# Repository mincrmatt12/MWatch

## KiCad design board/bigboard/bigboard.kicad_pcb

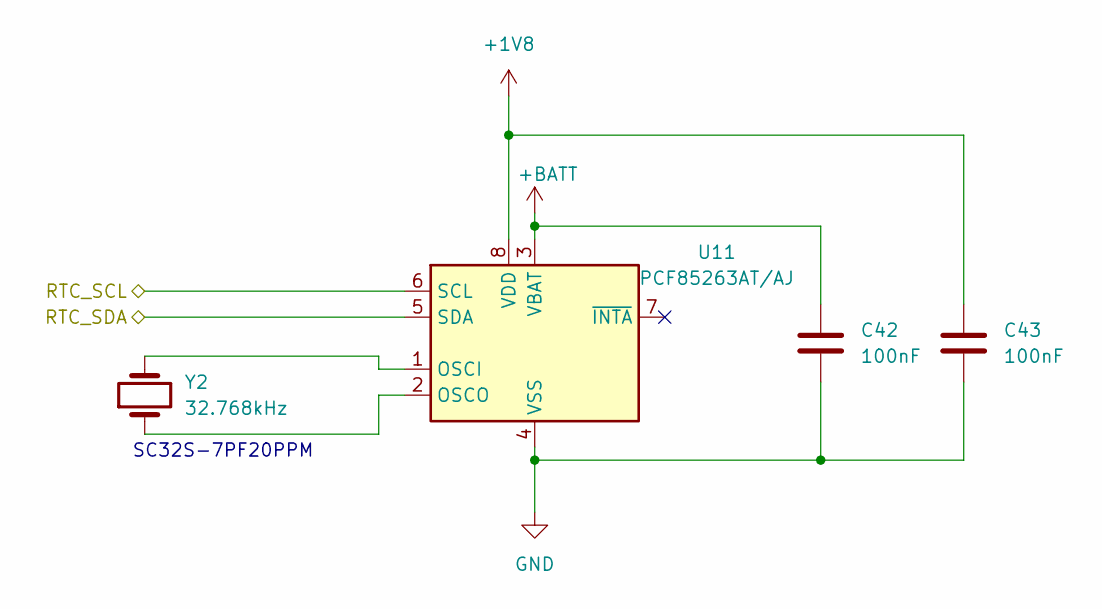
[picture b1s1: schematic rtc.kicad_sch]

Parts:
C42, C43: 100nF; C_0201_0603Metric; MPN CC0201KRX5R8BB104
U11: PCF85263AT/AJ; SOIC-8_3.9x4.9mm_P1.27mm; MPN PCF85263AT/AJ
Y2: 32.768kHz; Crystal_SMD_3215-2Pin_3.2x1.5mm; MPN SC32S-7PF20PPM

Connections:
+1V8: C43.1, U11.8 (VDD); also elsewhere on the board
+BATT: C42.1, U11.3 (VBAT); also elsewhere on the board
/BT/SCL_RTC: U11.6 (SCL); also elsewhere on the board
/BT/SDA_RTC: U11.5 (SDA); also elsewhere on the board
GND: C42.2, C43.2, U11.4 (VSS); also elsewhere on the board
unnamed: U11.1 (OSCI), Y2.2
unnamed: U11.2 (OSCO), Y2.1

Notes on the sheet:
SC32S-7PF20PPM

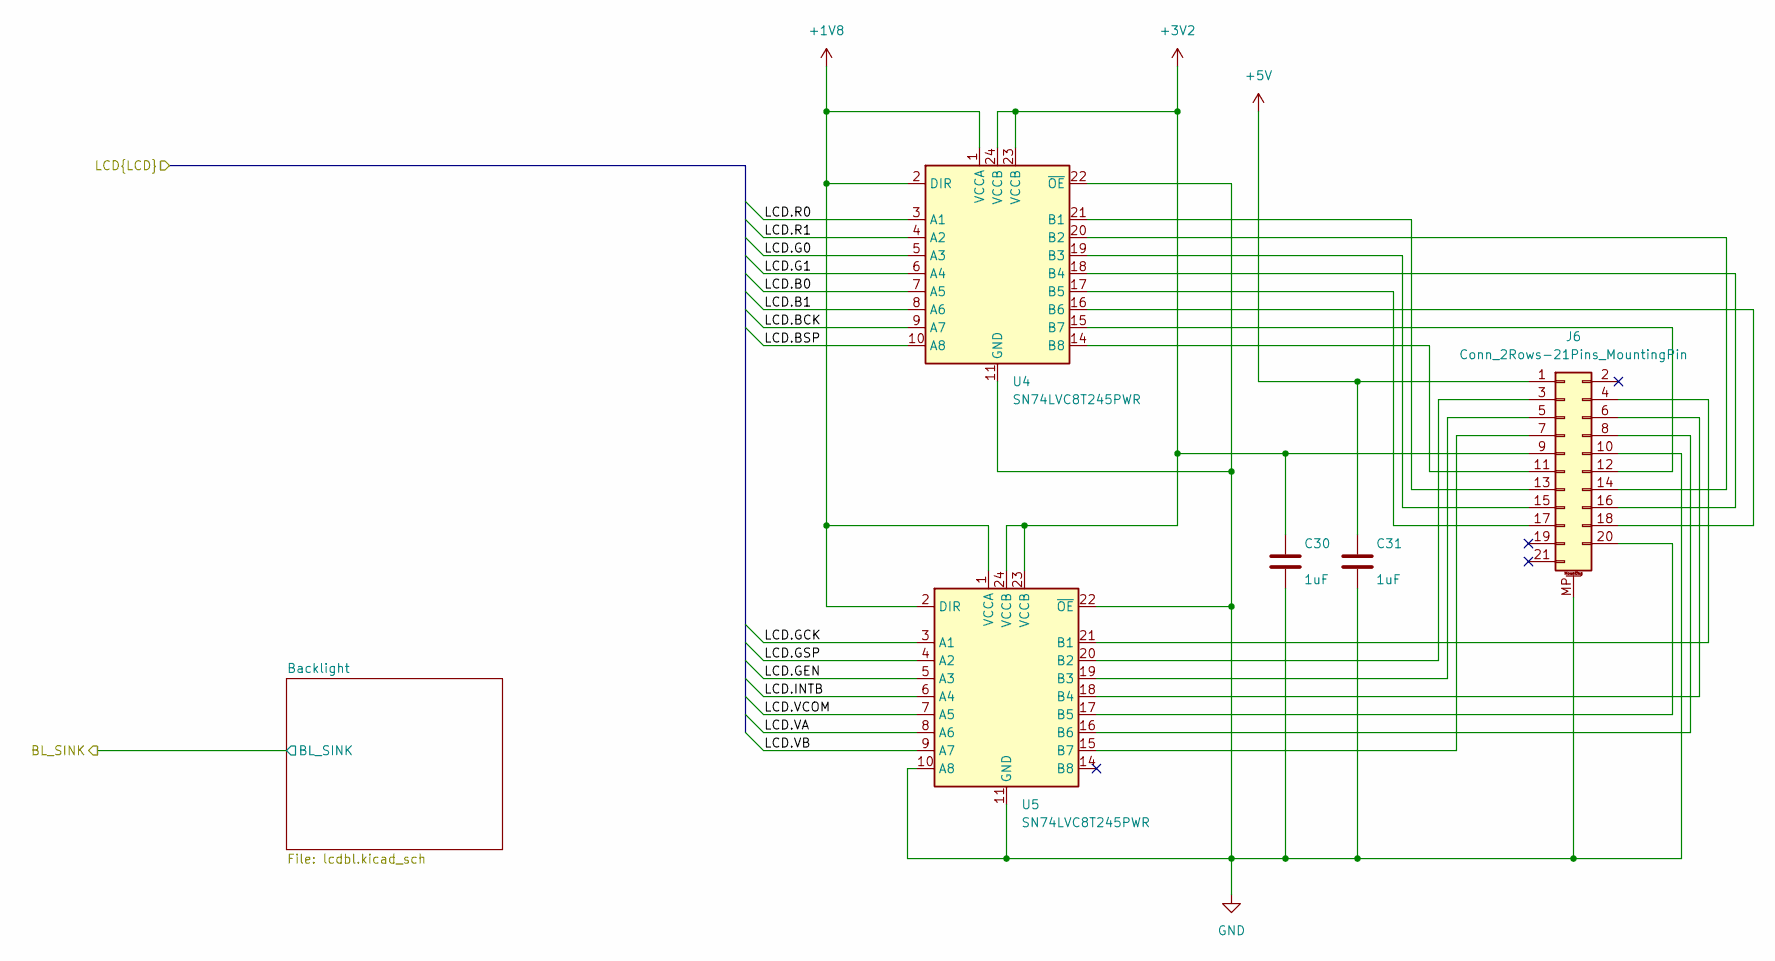
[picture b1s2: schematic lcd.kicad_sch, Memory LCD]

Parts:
C30, C31: 1uF; C_0201_0603Metric; MPN CC0201MRX5R6BB105
J6: Conn_2Rows-21Pins_MountingPin; 5035662102; MPN 503566-2102
U4, U5: SN74LVC8T245PWR; TSSOP-24_4.4x7.8mm_P0.65mm; MPN SN74LVC8T245PWR

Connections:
+1V8: U4.1 (VCCA), U4.2 (DIR), U5.1 (VCCA), U5.2 (DIR); also elsewhere on the board
+3V2: C30.1, J6.9, U4.23 (VCCB), U4.24 (VCCB), U5.23 (VCCB), U5.24 (VCCB); also elsewhere on the board
+5V: C31.1, J6.1; also elsewhere on the board
/LCD/LCD.B0: U4.7 (A5); also elsewhere on the board
/LCD/LCD.B1: U4.8 (A6); also elsewhere on the board
/LCD/LCD.BCK: U4.9 (A7); also elsewhere on the board
/LCD/LCD.BSP: U4.10 (A8); also elsewhere on the board
/LCD/LCD.G0: U4.5 (A3); also elsewhere on the board
/LCD/LCD.G1: U4.6 (A4); also elsewhere on the board
/LCD/LCD.GCK: U5.3 (A1); also elsewhere on the board
/LCD/LCD.GEN: U5.5 (A3); also elsewhere on the board
/LCD/LCD.GSP: U5.4 (A2); also elsewhere on the board
/LCD/LCD.INTB: U5.6 (A4); also elsewhere on the board
/LCD/LCD.R0: U4.3 (A1); also elsewhere on the board
/LCD/LCD.R1: U4.4 (A2); also elsewhere on the board
/LCD/LCD.VA: U5.8 (A6); also elsewhere on the board
/LCD/LCD.VB: U5.7 (A5), U5.9 (A7); also elsewhere on the board
GND: C30.2, C31.2, J6.10, J6.MP (MountPin), U4.11 (GND), U4.12 (GND), U4.13 (GND), U4.22 (~OE), U5.10 (A8), U5.11 (GND), U5.12 (GND), U5.13 (GND), U5.22 (~OE); also elsewhere on the board
unnamed: J6.3, U5.20 (B2)
unnamed: J6.4, U5.21 (B1)
unnamed: J6.5, U5.19 (B3)
unnamed: J6.6, U5.18 (B4)
unnamed: J6.7, U5.15 (B7)
unnamed: J6.8, U5.16 (B6)
unnamed: J6.11, U4.14 (B8)
unnamed: J6.12, U4.15 (B7)
unnamed: J6.13, U4.21 (B1)
unnamed: J6.14, U4.20 (B2)
unnamed: J6.15, U4.19 (B3)
unnamed: J6.16, U4.18 (B4)
unnamed: J6.17, U4.17 (B5)
unnamed: J6.18, U4.16 (B6)
unnamed: J6.20, U5.17 (B5)

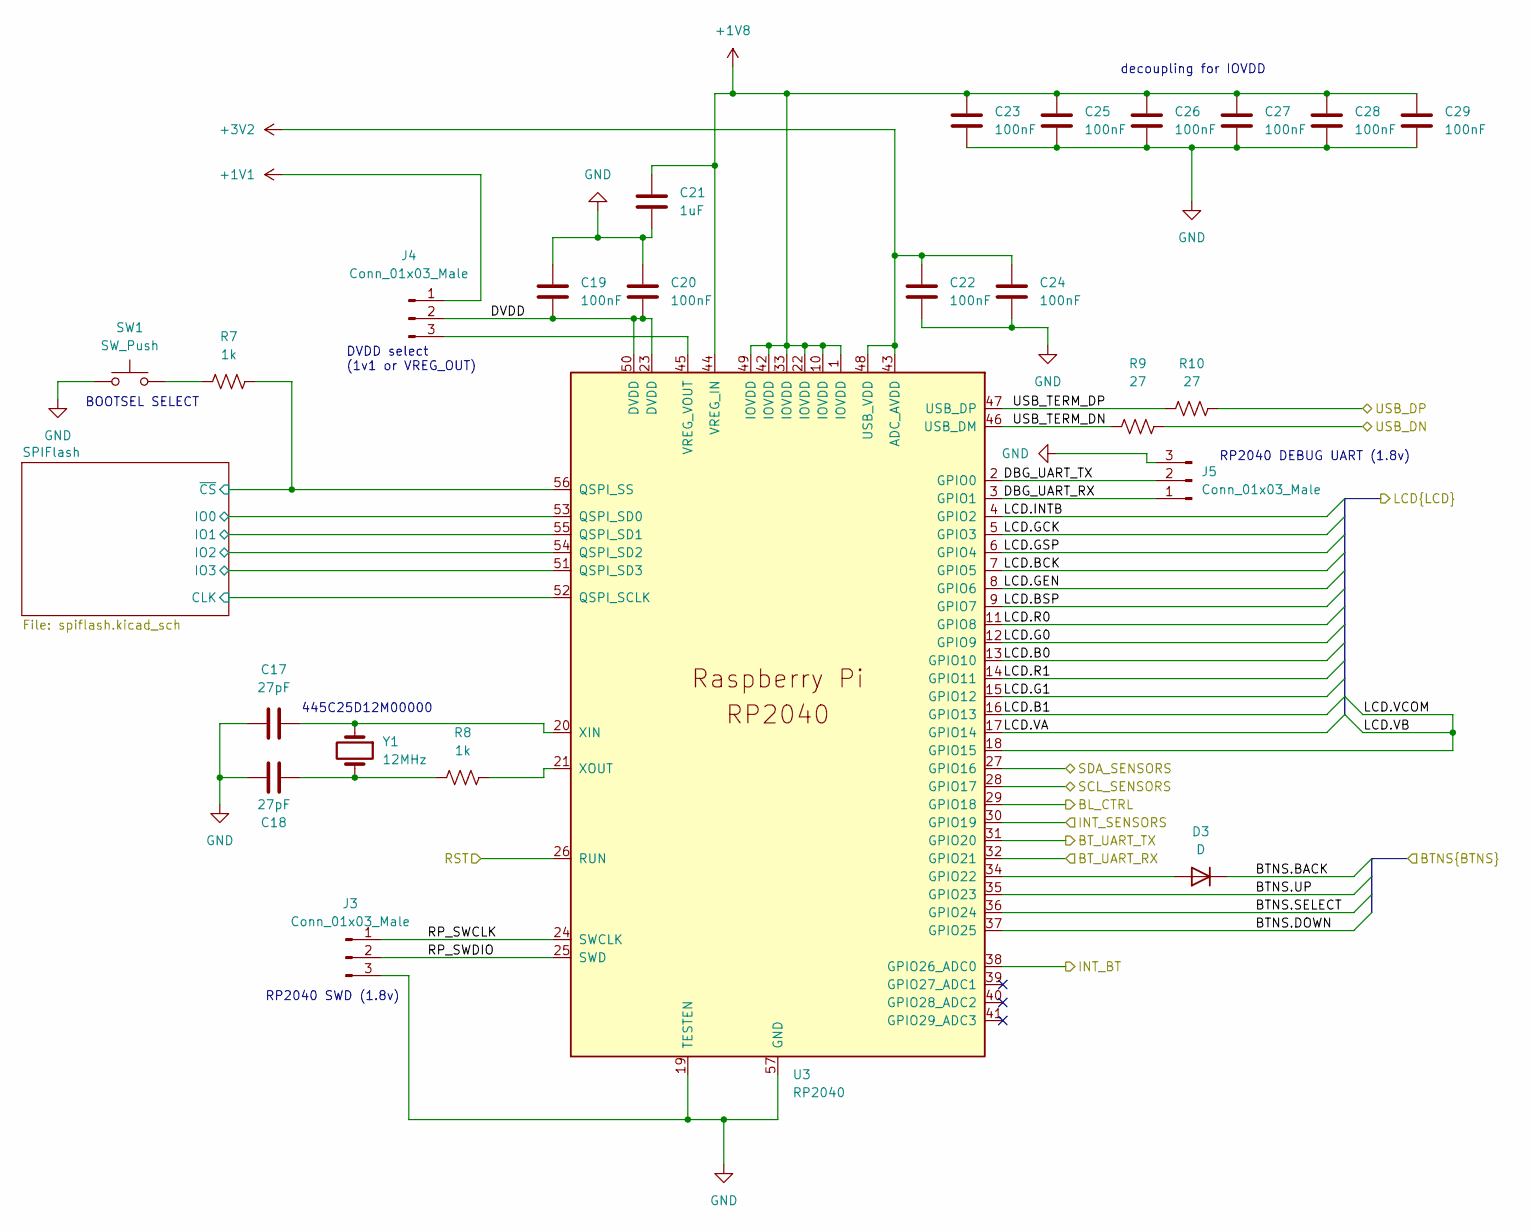
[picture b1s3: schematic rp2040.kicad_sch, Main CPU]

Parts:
C17, C18: 27pF; C_0201_0603Metric; MPN CC0201JRNPO9BN270
C19, C20, C22, C23, C24, C25, C26, C27, C28, C29: 100nF; C_0201_0603Metric; MPN CC0201KRX5R8BB104
C21: 1uF; C_0201_0603Metric; MPN CC0201MRX5R6BB105
D3: D; D_SOD-323; MPN CUS10S30,H3F
J3, J4, J5: Conn_01x03_Male; PinHeader_1x03_P2.54mm_Vertical
R7, R8: 1k; R_0201_0603Metric; MPN RC0201FR-071KL
R9, R10: 27; R_0201_0603Metric; MPN RC0201FR-0727RL
SW1: SW_Push; SW_PUSH_6mm; MPN B3F-1020
U3: RP2040; RP2040-QFN-56; MPN SC0914(7)
Y1: 12MHz; Crystal_SMD_5032-2Pin_5.0x3.2mm; MPN 445C25D12M00000

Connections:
+1V1: J4.1; also elsewhere on the board
+1V8: C21.1, C23.1, C25.1, C26.1, C27.1, C28.1, C29.1, U3.1 (IOVDD), U3.10 (IOVDD), U3.22 (IOVDD), U3.33 (IOVDD), U3.42 (IOVDD), U3.44 (VREG_IN), U3.49 (IOVDD); also elsewhere on the board
+3V2: C22.1, C24.1, U3.43 (ADC_AVDD), U3.48 (USB_VDD); also elsewhere on the board
/BT/BT_INT: U3.38 (GPIO26_ADC0); also elsewhere on the board
/BT/BT_UART_RX: U3.31 (GPIO20); also elsewhere on the board
/BT/BT_UART_TX: U3.32 (GPIO21); also elsewhere on the board
/ButtonsHaptics/BTNS.BACK: D3.1 (K); also elsewhere on the board
/ButtonsHaptics/BTNS.DOWN: U3.37 (GPIO25); also elsewhere on the board
/ButtonsHaptics/BTNS.SELECT: U3.36 (GPIO24); also elsewhere on the board
/ButtonsHaptics/BTNS.UP: U3.35 (GPIO23); also elsewhere on the board
/DbgResets/RP2040_RST: U3.26 (RUN); also elsewhere on the board
/LCD/LCD.B0: U3.13 (GPIO10); also elsewhere on the board
/LCD/LCD.B1: U3.16 (GPIO13); also elsewhere on the board
/LCD/LCD.BCK: U3.7 (GPIO5); also elsewhere on the board
/LCD/LCD.BSP: U3.9 (GPIO7); also elsewhere on the board
/LCD/LCD.G0: U3.12 (GPIO9); also elsewhere on the board
/LCD/LCD.G1: U3.15 (GPIO12); also elsewhere on the board
/LCD/LCD.GCK: U3.5 (GPIO3); also elsewhere on the board
/LCD/LCD.GEN: U3.8 (GPIO6); also elsewhere on the board
/LCD/LCD.GSP: U3.6 (GPIO4); also elsewhere on the board
/LCD/LCD.INTB: U3.4 (GPIO2); also elsewhere on the board
/LCD/LCD.R0: U3.11 (GPIO8); also elsewhere on the board
/LCD/LCD.R1: U3.14 (GPIO11); also elsewhere on the board
/LCD/LCD.VA: U3.17 (GPIO14); also elsewhere on the board
/LCD/LCD.VB: U3.18 (GPIO15); also elsewhere on the board
/Power/BL_CTRL/IO1: U3.29 (GPIO18); also elsewhere on the board
/Power/USB_DN: R9.2; also elsewhere on the board
/Power/USB_DP: R10.2; also elsewhere on the board
/RP2040/DBG_UART_RX: J5.1, U3.3 (GPIO1)
/RP2040/DBG_UART_TX: J5.2, U3.2 (GPIO0)
/RP2040/DVDD: C19.2, C20.2, J4.2, U3.23 (DVDD), U3.50 (DVDD)
/RP2040/INT_SENSORS: U3.30 (GPIO19); also elsewhere on the board
/RP2040/RP_SWCLK: J3.1, U3.24 (SWCLK)
/RP2040/RP_SWDIO: J3.2, U3.25 (SWD)
/RP2040/SCL_SENSORS: U3.28 (GPIO17); also elsewhere on the board
/RP2040/SDA_SENSORS: U3.27 (GPIO16); also elsewhere on the board
/RP2040/SPIFlash/CLK: U3.52 (QSPI_SCLK); also elsewhere on the board
/RP2040/SPIFlash/IO0: U3.53 (QSPI_SD0); also elsewhere on the board
/RP2040/SPIFlash/IO1: U3.55 (QSPI_SD1); also elsewhere on the board
/RP2040/SPIFlash/IO2: U3.54 (QSPI_SD2); also elsewhere on the board
/RP2040/SPIFlash/IO3: U3.51 (QSPI_SD3); also elsewhere on the board
/RP2040/SPIFlash/~CS: R7.2, U3.56 (QSPI_SS); also elsewhere on the board
/RP2040/USB_TERM_DN: R9.1, U3.46 (USB_DM)
/RP2040/USB_TERM_DP: R10.1, U3.47 (USB_DP)
GND: C17.1, C18.1, C19.1, C20.1, C21.2, C22.2, C23.2, C24.2, C25.2, C26.2, C27.2, C28.2, C29.2, J3.3, J5.3, SW1.1, U3.19 (TESTEN), U3.57 (GND); also elsewhere on the board
unnamed: C18.2, R8.1, Y1.2
unnamed: D3.2 (A), U3.34 (GPIO22)
unnamed: J4.3, U3.45 (VREG_VOUT)
unnamed: R7.1, SW1.2
unnamed: C17.2, U3.20 (XIN), Y1.1
unnamed: R8.2, U3.21 (XOUT)

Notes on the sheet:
decoupling for IOVDD
RP2040 SWD (1.8v)
445C25D12M00000
RP2040 DEBUG UART (1.8v)
DVDD select (1v1 or VREG_OUT)
BOOTSEL SELECT

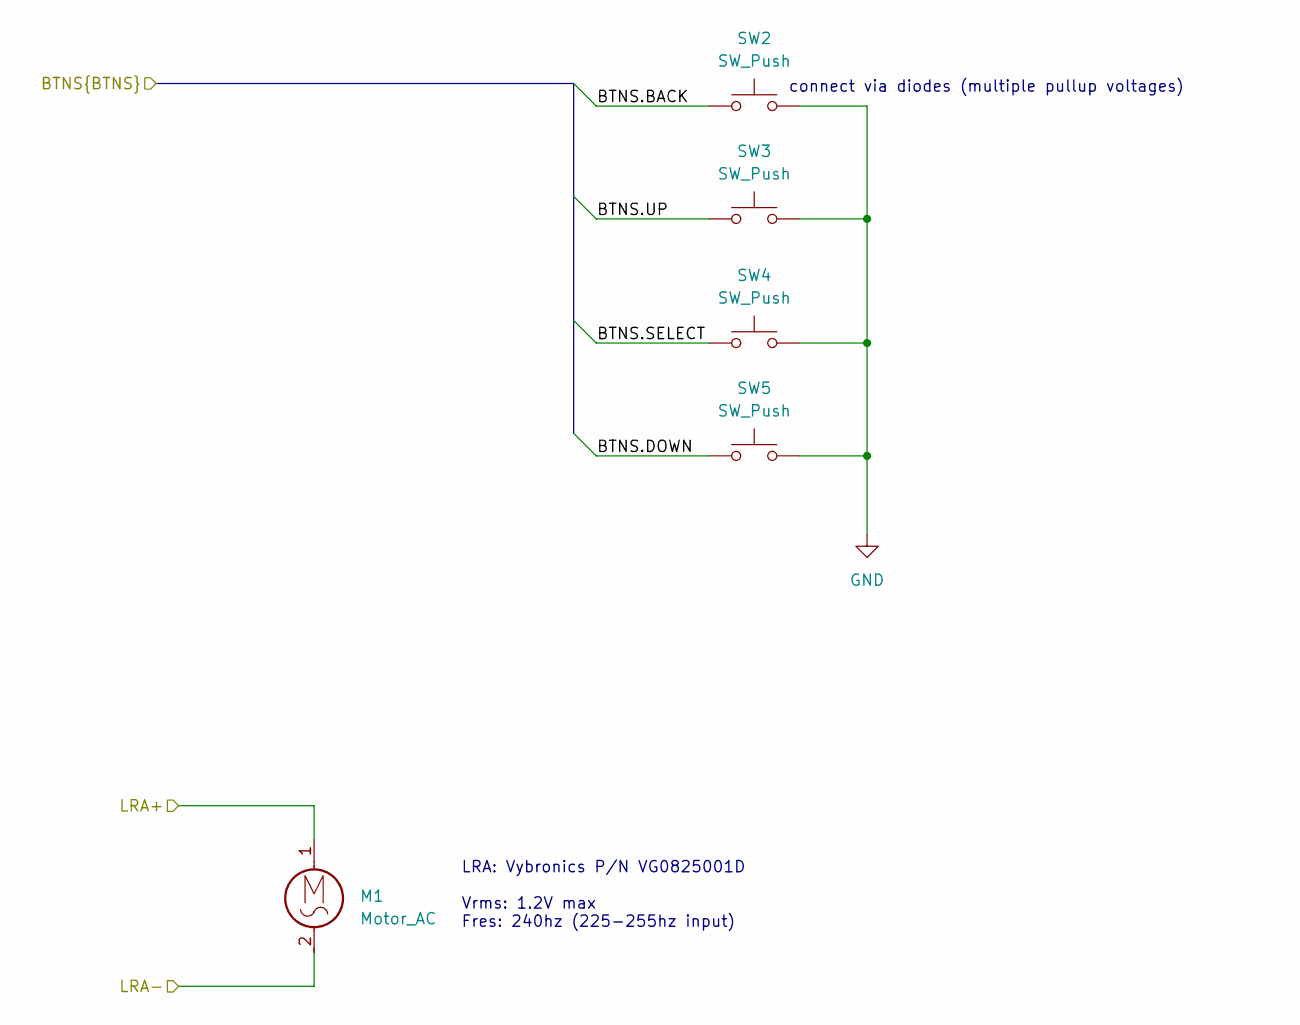
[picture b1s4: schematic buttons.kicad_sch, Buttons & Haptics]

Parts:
M1: Motor_AC; TerminalBlock_TE_282834-2_1x02_P2.54mm_Horizontal
SW2, SW3, SW4, SW5: SW_Push; SW_PUSH_6mm; MPN B3F-1020

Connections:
/ButtonsHaptics/BTNS.BACK: SW2.1; also elsewhere on the board
/ButtonsHaptics/BTNS.DOWN: SW5.1; also elsewhere on the board
/ButtonsHaptics/BTNS.SELECT: SW4.1; also elsewhere on the board
/ButtonsHaptics/BTNS.UP: SW3.1; also elsewhere on the board
/ButtonsHaptics/LRA+: M1.1; also elsewhere on the board
/ButtonsHaptics/LRA-: M1.2; also elsewhere on the board
GND: SW2.2, SW3.2, SW4.2, SW5.2; also elsewhere on the board

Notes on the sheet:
connect via diodes (multiple pullup voltages)
LRA: Vybronics P/N VG0825001D Vrms: 1.2V max Fres: 240hz (225-255hz input)

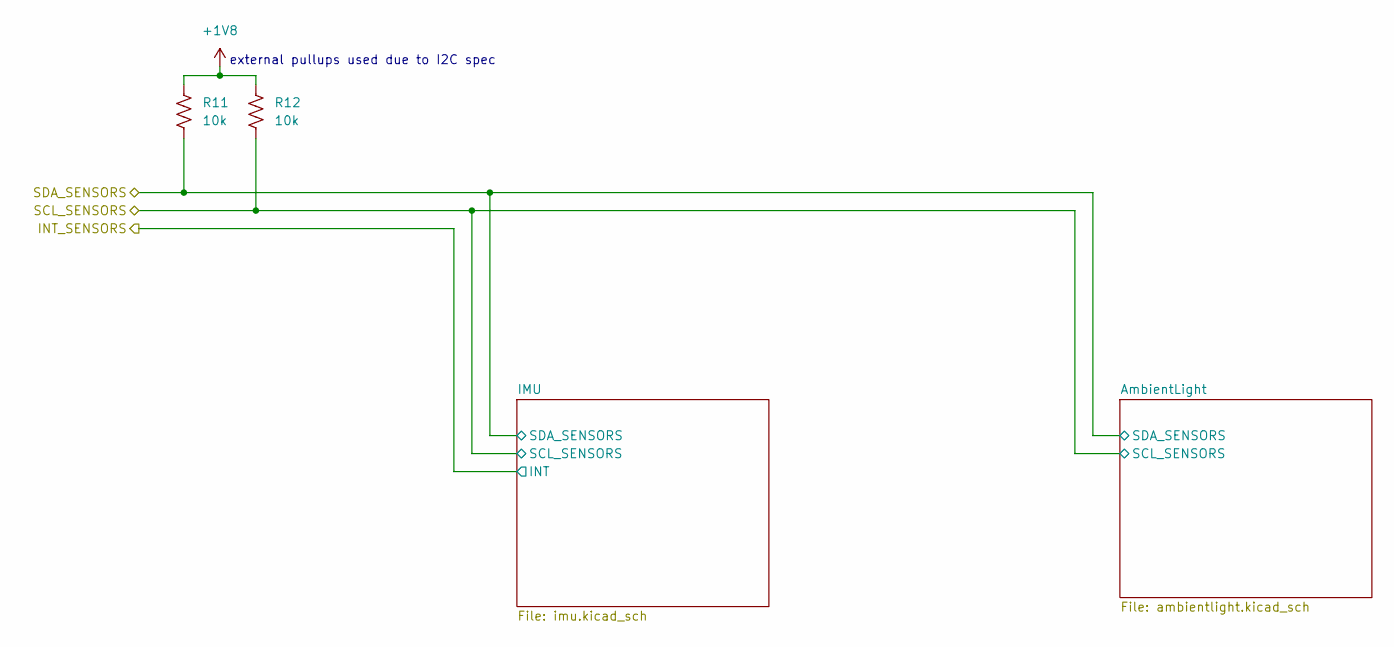
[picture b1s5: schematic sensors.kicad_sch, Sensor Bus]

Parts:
R11, R12: 10k; R_0201_0603Metric; MPN RC0201FR-0710KL

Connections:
+1V8: R11.1, R12.1; also elsewhere on the board
/RP2040/SCL_SENSORS: R12.2; also elsewhere on the board
/RP2040/SDA_SENSORS: R11.2; also elsewhere on the board

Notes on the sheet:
external pullups used due to I2C spec

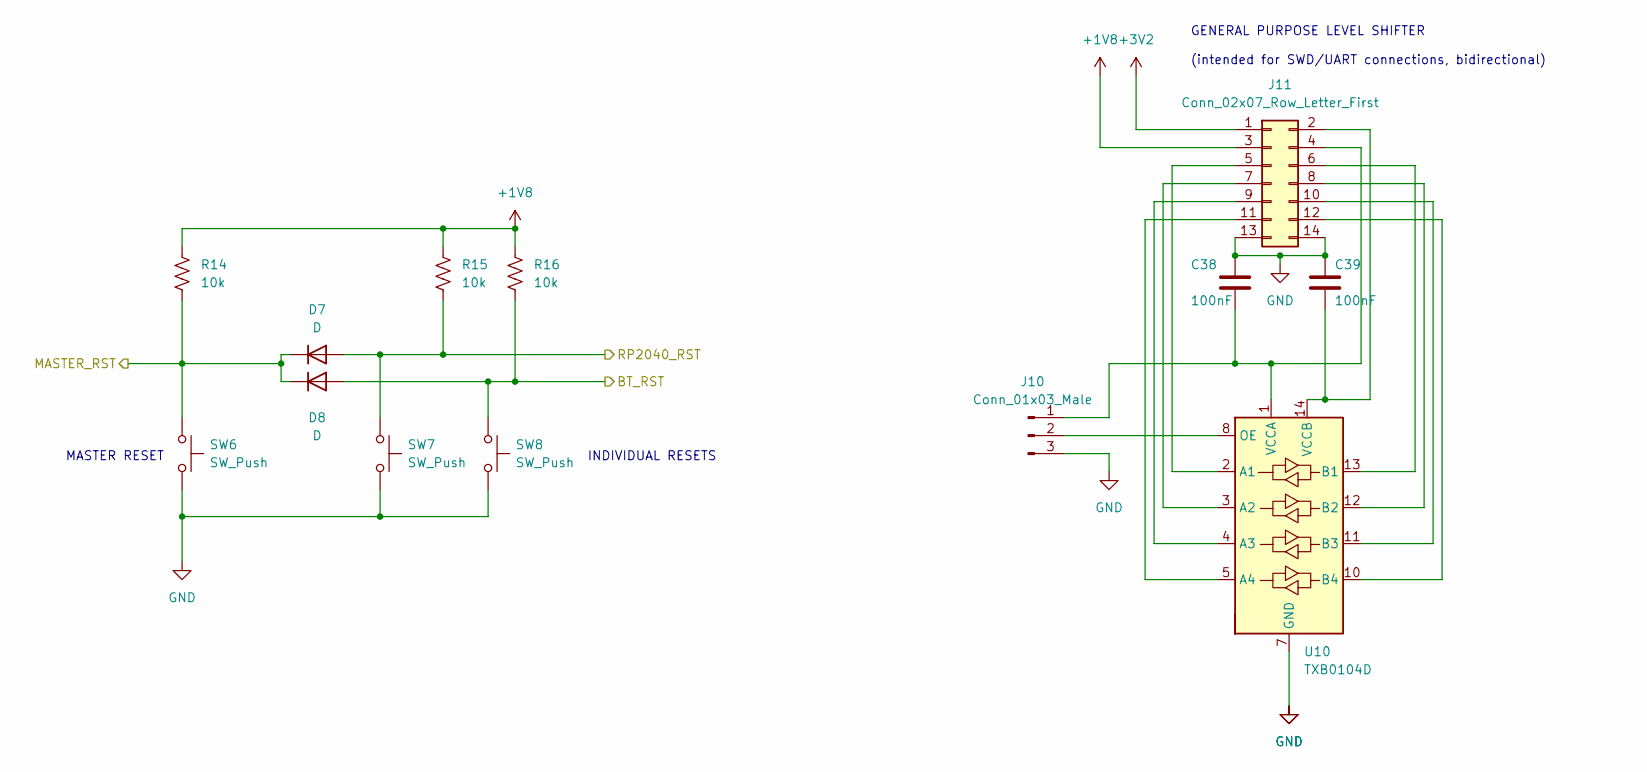
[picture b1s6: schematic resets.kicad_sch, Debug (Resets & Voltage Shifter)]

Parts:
C38, C39: 100nF; C_0201_0603Metric; MPN CC0201KRX5R8BB104
D7, D8: D; D_SOD-323; MPN CUS10S30,H3F
J10: Conn_01x03_Male; PinHeader_1x03_P2.54mm_Vertical
J11: Conn_02x07_Row_Letter_First; PinHeader_2x07_P2.54mm_Vertical
R14, R15, R16: 10k; R_0201_0603Metric; MPN RC0201FR-0710KL
SW6, SW7, SW8: SW_Push; SW_PUSH_6mm; MPN B3F-1020
U10: TXB0104D; SOIC-14_3.9x8.7mm_P1.27mm; MPN TXB0104D

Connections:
+1V8: J11.3, R14.1, R15.1, R16.1; also elsewhere on the board
+3V2: J11.1; also elsewhere on the board
/BT/RST: D8.2 (A), R16.2, SW8.1; also elsewhere on the board
/DbgResets/MASTER_RST: D7.1 (K), D8.1 (K), R14.2, SW6.1; also elsewhere on the board
/DbgResets/RP2040_RST: D7.2 (A), R15.2, SW7.1; also elsewhere on the board
GND: C38.1, C39.1, J10.3, J11.13, J11.14, SW6.2, SW7.2, SW8.2, U10.7 (GND); also elsewhere on the board
unnamed: C38.2, J10.1, J11.4, U10.1 (VCCA)
unnamed: J10.2, U10.8 (OE)
unnamed: C39.2, J11.2, U10.14 (VCCB)
unnamed: J11.5, U10.2 (A1)
unnamed: J11.6, U10.13 (B1)
unnamed: J11.7, U10.3 (A2)
unnamed: J11.8, U10.12 (B2)
unnamed: J11.9, U10.4 (A3)
unnamed: J11.10, U10.11 (B3)
unnamed: J11.11, U10.5 (A4)
unnamed: J11.12, U10.10 (B4)

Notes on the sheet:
INDIVIDUAL RESETS
MASTER RESET
GENERAL PURPOSE LEVEL SHIFTER (intended for SWD/UART connections, bidirectional)

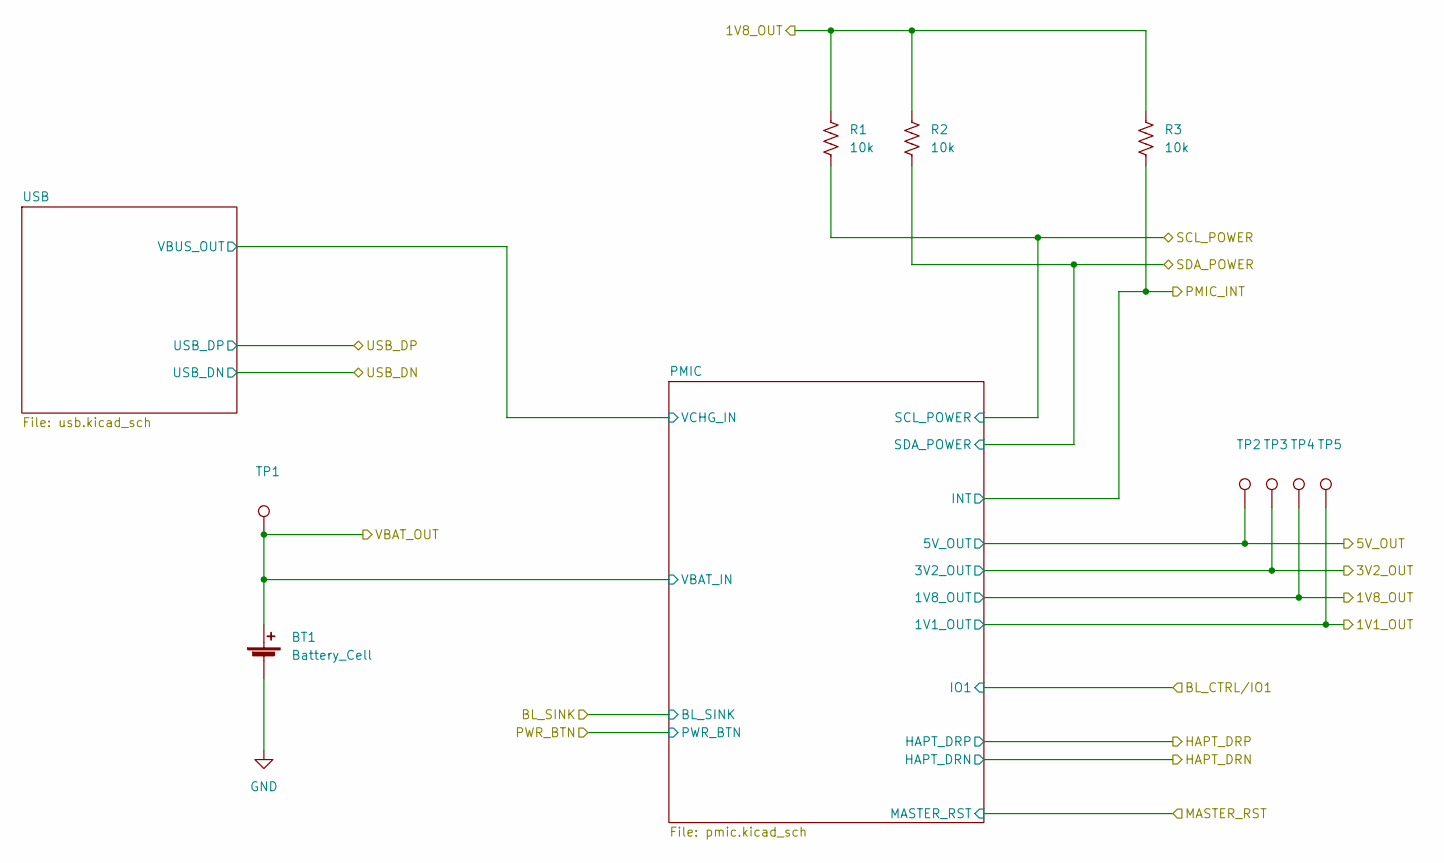
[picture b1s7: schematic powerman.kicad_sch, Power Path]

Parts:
BT1: Battery_Cell; JST_PH_B3B-PH-K_1x03_P2.00mm_Vertical; MPN B3B-PH-K-S(LF)(SN)
R1, R2, R3: 10k; R_0201_0603Metric; MPN RC0201FR-0710KL
TP1, TP2, TP3, TP4, TP5: TestPoint; TestPoint_Pad_D2.5mm

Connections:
+1V1: TP5.1; also elsewhere on the board
+1V8: R1.1, R2.1, R3.1, TP4.1; also elsewhere on the board
+3V2: TP3.1; also elsewhere on the board
+5V: TP2.1; also elsewhere on the board
+BATT: BT1.1 (+), TP1.1; also elsewhere on the board
/BT/PMIC_INT: R3.2; also elsewhere on the board
/BT/SCL_POWER: R1.2; also elsewhere on the board
/BT/SDA_POWER: R2.2; also elsewhere on the board
GND: BT1.2 (-); also elsewhere on the board

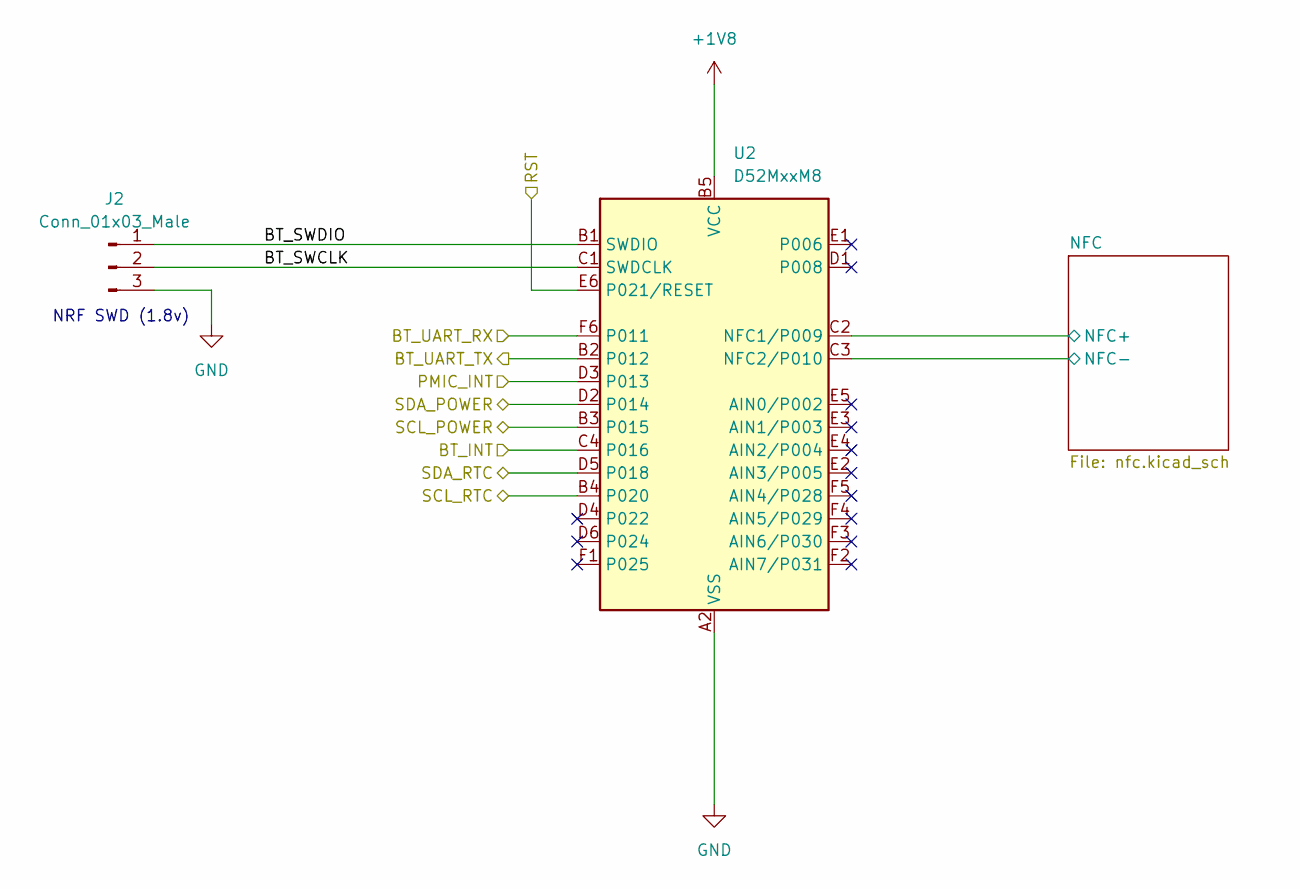
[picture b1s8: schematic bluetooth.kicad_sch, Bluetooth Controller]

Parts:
J2: Conn_01x03_Male; PinHeader_1x03_P2.54mm_Vertical
U2: D52MxxM8; Garmin_M8-35_9.8x14.0mm_Layout6x6_P1.5mm; MPN D52MD2M8IA-TRAY

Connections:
+1V8: U2.B5 (VCC), U2.B6 (VCC), U2.C5 (VCC), U2.C6 (VCC); also elsewhere on the board
/BT/BT_INT: U2.C4 (P016); also elsewhere on the board
/BT/BT_SWCLK: J2.2, U2.C1 (SWDCLK)
/BT/BT_SWDIO: J2.1, U2.B1 (SWDIO)
/BT/BT_UART_RX: U2.F6 (P011); also elsewhere on the board
/BT/BT_UART_TX: U2.B2 (P012); also elsewhere on the board
/BT/NFC/NFC+: U2.C2 (NFC1/P009); also elsewhere on the board
/BT/NFC/NFC-: U2.C3 (NFC2/P010); also elsewhere on the board
/BT/PMIC_INT: U2.D3 (P013); also elsewhere on the board
/BT/RST: U2.E6 (P021/RESET); also elsewhere on the board
/BT/SCL_POWER: U2.B3 (P015); also elsewhere on the board
/BT/SCL_RTC: U2.B4 (P020); also elsewhere on the board
/BT/SDA_POWER: U2.D2 (P014); also elsewhere on the board
/BT/SDA_RTC: U2.D5 (P018); also elsewhere on the board
GND: J2.3, U2.A2 (VSS), U2.A3 (VSS), U2.A4 (VSS), U2.A5 (VSS), U2.A6 (VSS); also elsewhere on the board

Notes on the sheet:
NRF SWD (1.8v)

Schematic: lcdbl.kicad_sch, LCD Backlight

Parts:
D4, D5, D6: LED; LED_0603_1608Metric; MPN BZ-C0603-C2-E1
J7: Conn_01x05_Male; PinHeader_1x05_P2.54mm_Vertical
J8: Conn_02x03_Row_Letter_First; PinHeader_2x03_P2.54mm_Vertical

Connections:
+1V8: J7.5; also elsewhere on the board
+3V2: J7.3; also elsewhere on the board
+5V: J7.1; also elsewhere on the board
/LCD/BL_SINK: D4.1 (K), D5.1 (K), D6.1 (K); also elsewhere on the board
/LCD/Backlight/VLED: J7.2, J7.4, J8.1, J8.3, J8.5
unnamed: D4.2 (A), J8.2
unnamed: D5.2 (A), J8.4
unnamed: D6.2 (A), J8.6

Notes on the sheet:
LED ENABLE
BACKLIGHT VOLTAGE SELECT

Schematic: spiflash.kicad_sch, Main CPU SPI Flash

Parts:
C32: 100nF; C_0201_0603Metric; MPN CC0201KRX5R8BB104
J9: Conn_01x02_Male; PinHeader_1x02_P2.54mm_Vertical
R13: 10k; R_0201_0603Metric; MPN RC0201FR-0710KL
U6: GD25LQ128DSIGR; SOIC-8_5.23x5.23mm_P1.27mm; MPN GD25LQ128DSIGR

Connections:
+1V8: C32.1, R13.2, U6.8 (VCC); also elsewhere on the board
/RP2040/SPIFlash/CLK: U6.6 (CLK); also elsewhere on the board
/RP2040/SPIFlash/IO0: U6.5 (DI(IO0)); also elsewhere on the board
/RP2040/SPIFlash/IO1: U6.2 (DO(IO1)); also elsewhere on the board
/RP2040/SPIFlash/IO2: U6.3 (IO2); also elsewhere on the board
/RP2040/SPIFlash/IO3: U6.7 (IO3); also elsewhere on the board
/RP2040/SPIFlash/~CS: J9.2, U6.1 (~CS); also elsewhere on the board
GND: C32.2, U6.4 (GND); also elsewhere on the board
unnamed: J9.1, R13.1

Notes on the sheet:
FLASH CS PULLUP ENABLE

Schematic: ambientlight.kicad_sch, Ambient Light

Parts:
C37: 1uF; C_0201_0603Metric; MPN CC0201MRX5R6BB105
U9: APDS-9306-065; Broadcom_DFN-6_2x2mm_P0.65mm; MPN APDS-9306-065

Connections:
+1V8: C37.1, U9.3 (VDD); also elsewhere on the board
/RP2040/SCL_SENSORS: U9.1 (SCL); also elsewhere on the board
/RP2040/SDA_SENSORS: U9.2 (SDA); also elsewhere on the board
GND: C37.2, U9.6 (GND); also elsewhere on the board

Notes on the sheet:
I2C: 0x52

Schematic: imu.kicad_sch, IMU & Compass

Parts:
C33, C34, C35, C36: 100nF; C_0201_0603Metric; MPN CC0201KRX5R8BB104
U7: BMM150; WLCSP-12_1.56x1.56mm_P0.4mm; MPN BMM150
U8: BMI270; Bosch_LGA-14_3x2.5mm_P0.5mm; MPN BMI270

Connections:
+1V8: C33.1, C34.1, C35.1, C36.1, U7.A1 (PS), U7.B2 (VDDIO), U7.E5 (VDD), U8.5 (VDDIO), U8.8 (VDD), U8.12 (CSB); also elsewhere on the board
/RP2040/INT_SENSORS: U7.D2 (INT), U8.4 (INT1); also elsewhere on the board
/RP2040/SCL_SENSORS: U7.A3 (SCK), U8.13 (SCx); also elsewhere on the board
/RP2040/SDA_SENSORS: U7.B4 (SDI), U8.14 (SDx); also elsewhere on the board
GND: C33.2, C34.2, C35.2, C36.2, U7.A5 (CSB), U7.C1 (SDO), U7.C5 (GND), U7.E1 (GND), U7.E3 (GND), U8.1 (SDO), U8.6 (GNDIO), U8.7 (GND); also elsewhere on the board

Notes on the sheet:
I2C: 0x10
note: pin-compatible with BMI160
I2C: 0x68

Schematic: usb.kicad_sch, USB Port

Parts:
D1: SP0502BAHTG; SOT-23; MPN SP0502BAHTG
J1: USB_C_Receptacle_USB2.0; USB_C_Receptacle_XKB_U262-16XN-4BVC11; MPN U262-161N-4BVC11
R4, R5: 5.1k; R_0201_0603Metric; MPN RC0201FR-075K1L

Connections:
/Power/PMIC/VCHG_IN: J1.A4 (VBUS), J1.A9 (VBUS), J1.B4 (VBUS), J1.B9 (VBUS); also elsewhere on the board
/Power/USB_DN: D1.1 (K), J1.A7 (D-), J1.B7 (D-); also elsewhere on the board
/Power/USB_DP: D1.2 (K), J1.A6 (D+), J1.B6 (D+); also elsewhere on the board
GND: D1.3 (A), J1.A1 (GND), J1.A12 (GND), J1.B1 (GND), J1.B12 (GND), J1.S1 (SHIELD), R4.2, R5.2; also elsewhere on the board
unnamed: J1.A5 (CC1), R5.1
unnamed: J1.B5 (CC2), R4.1

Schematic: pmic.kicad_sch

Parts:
C1: 1uF; C_0603_1608Metric; MPN CC0603KRX5R7BB105
C2, C4, C6, C7, C8, C11, C16: 100nF; C_0201_0603Metric; MPN CC0201KRX5R8BB104
C3, C5, C12: 1uF; C_0201_0603Metric; MPN CC0201MRX5R6BB105
C9, C10, C13, C14, C15: 10uF; C_0603_1608Metric; MPN GRM188R61E106KA73D
D2: D; D_SOD-323; MPN CUS10S30,H3F
L1: 4.7uH; L_0805_2012Metric; MPN MLP2012V4R7MT0S1
L2, L3: 2.2uH; L_0805_2012Metric; MPN DFE201210U-2R2M=P2
R6: 4.02k; R_0201_0603Metric; MPN RC0201FR-074K02L
U1: MAX20353AEWN+; MAX20353AEWN&plus_; MPN MAX20353AEWN+

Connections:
+1V1: C11.1, C13.1, L3.2, U1.B7 (BK2OUT); also elsewhere on the board
+1V8: C14.1, C16.1, L2.2, U1.G7 (BK1OUT); also elsewhere on the board
+3V2: C8.1, C12.1, U1.A5 (L2OUT); also elsewhere on the board
+5V: C7.1, C15.1, U1.C7 (BBOUT); also elsewhere on the board
+BATT: C2.1, U1.H3 (BAT); also elsewhere on the board
/BT/PMIC_INT: U1.G2 (*INT); also elsewhere on the board
/BT/SCL_POWER: U1.B1 (SCL); also elsewhere on the board
/BT/SDA_POWER: U1.B2 (SDA); also elsewhere on the board
/ButtonsHaptics/BTNS.BACK: D2.1 (K); also elsewhere on the board
/ButtonsHaptics/LRA+: U1.A2 (DRP); also elsewhere on the board
/ButtonsHaptics/LRA-: U1.A1 (DRN); also elsewhere on the board
/DbgResets/MASTER_RST: U1.F6 (*RST); also elsewhere on the board
/LCD/BL_SINK: U1.E1 (LED0); also elsewhere on the board
/Power/BL_CTRL/IO1: U1.C4 (MPC1); also elsewhere on the board
/Power/PMIC/VCHG_IN: C1.1, U1.H5 (CHGIN); also elsewhere on the board
GND: C1.2, C2.2, C3.2, C4.2, C5.2, C6.2, C7.2, C8.2, C9.2, C10.2, C11.2, C12.2, C13.2, C14.2, C15.2, C16.2, R6.1, U1.A3 (HDGND), U1.A6 (BK2GND), U1.C2 (DGND), U1.D3 (GSUB), U1.D5 (CTG), U1.D6 (QSTRT), U1.D7 (BBGND), U1.E5 (AGND), U1.G1 (BSTGND), U1.H6 (BK1GND); also elsewhere on the board
unnamed: D2.2 (A), U1.D2 (PFN1)
unnamed: L1.1, U1.E7 (BBHVLX)
unnamed: L1.2, U1.F7 (BBLVLX)
unnamed: L2.1, U1.H7 (BK1LX)
unnamed: L3.1, U1.A7 (BK2LX)
unnamed: C3.1, U1.E4 (CAP)
unnamed: C4.1, U1.C6 (CELL)
unnamed: C6.1, C9.1, C10.1, U1.A4 (SYS), U1.B6 (L2IN), U1.H4 (SYS)
unnamed: R6.2, U1.F3 (SET)
unnamed: C5.1, U1.D4 (VDIG)

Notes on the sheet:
I2C: 0x28 (main) / 0x36 (fuel gauge)

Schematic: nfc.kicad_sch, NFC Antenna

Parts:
AE1: Antenna_Loop; TerminalBlock_TE_282834-2_1x02_P2.54mm_Horizontal
C40, C41: 120pF; C_0201_0603Metric; MPN GRM0335C1H121JA01J

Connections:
/BT/NFC/NFC+: AE1.2, C41.1; also elsewhere on the board
/BT/NFC/NFC-: AE1.1, C40.1; also elsewhere on the board
GND: C40.2, C41.2; also elsewhere on the board

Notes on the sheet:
EXPECTED ANTENNA: Molex P/N 1462360151 La: 2.10uH Ra: 3.6 Ca: 1pF Q: 50.4

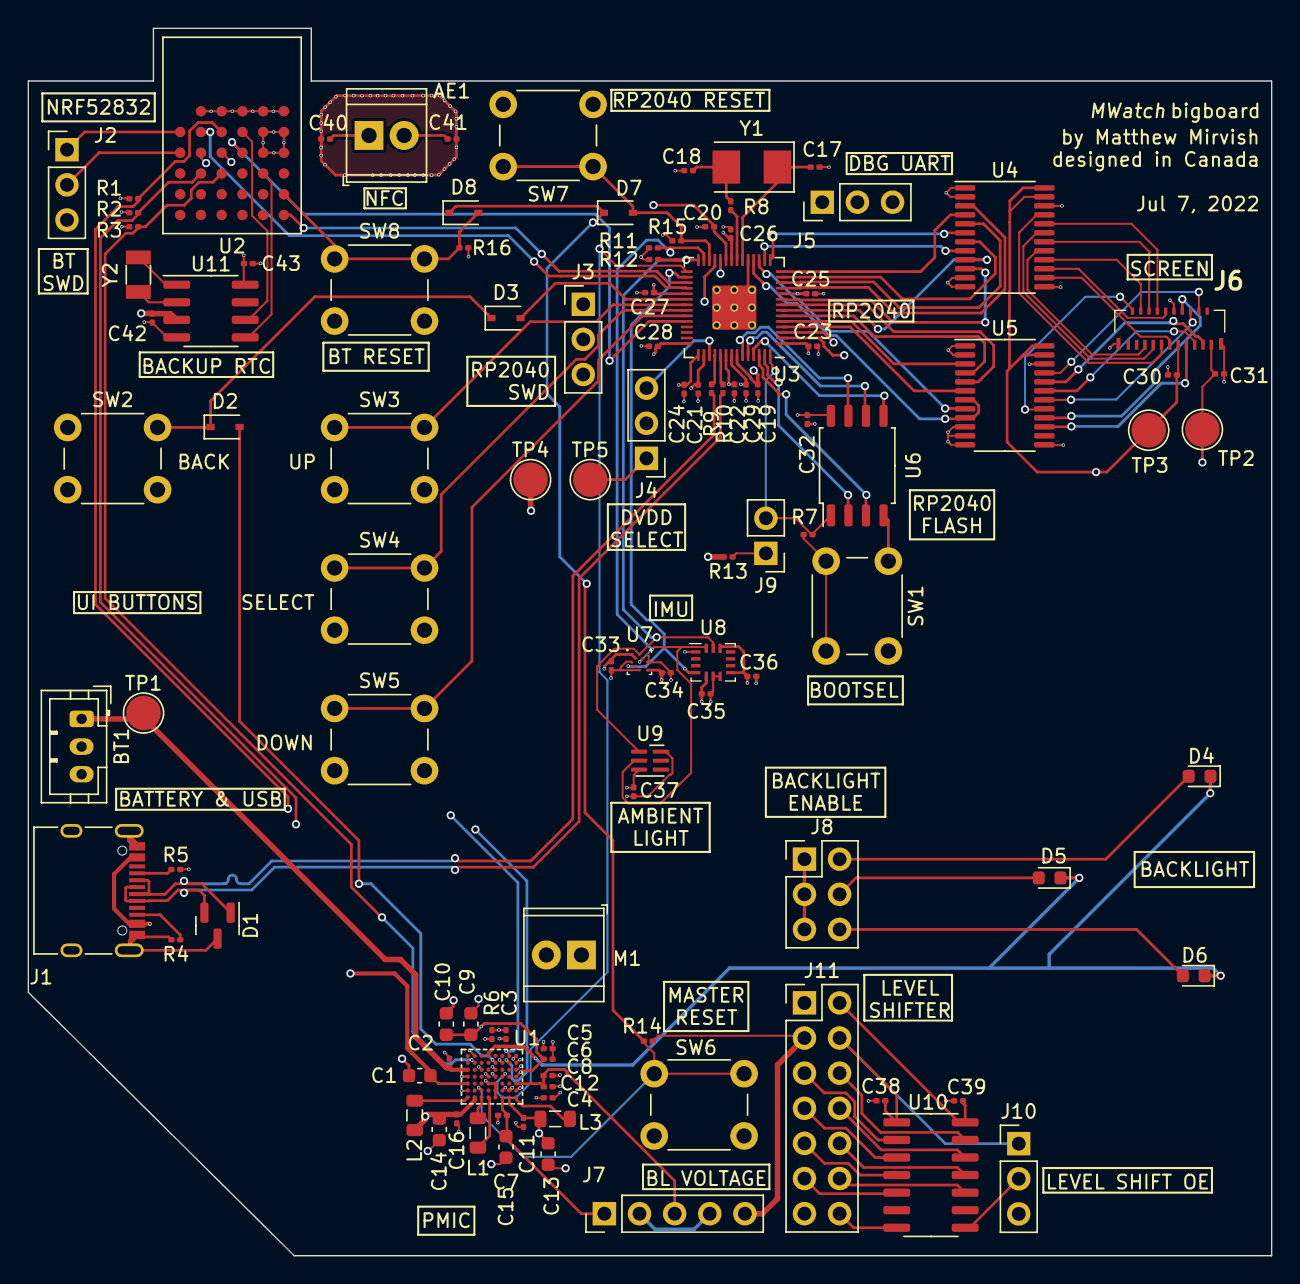
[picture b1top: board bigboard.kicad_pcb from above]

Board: 4 copper layers, 89.9 x 88.8 mm, 110 parts (0 on the bottom side), 113 nets.

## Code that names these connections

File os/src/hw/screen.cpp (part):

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
		/*
		 * VCLK
		 * GPIO2  -  INTB (cpu controlled)
		 * GPIO3  -  GCK
		 * GPIO4  -  GSP
		 *
		 * ----
		 *
		 * HCLK
		 * GPIO5  -  BCK
		 * GPIO6  -  GEN
		 * GPIO7  -  BSP
		 *
		 * ---
		 *
		 * DATAOUT
		 * GPIO8    - R0
		 * GPIO9    - G0
		 * GPIO10   - B0
		 * GPIO11   - R1
		 * GPIO12   - G1
		 * GPIO13   - B1
		 *
		 */
		pio_sm_set_consecutive_pindirs(pio, 0, 2, 3, true); 
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		//
		// on pins 14/15 / pwm 7
		//
		// VA      -- GPIO14
		// VB/VCOM -- GPIO15
		// roughly targeting 10hz (in power saving mode we might hae a slow enough clock to goto the min of 0.25hz but in 96mhz mode we don't)

		gpio_set_function(14, GPIO_FUNC_PWM);
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
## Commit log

2022-05-28 Initial commit: nonworking screen
2022-05-29 Working display init
    (in logic analyzer)
2022-07-07 Original board rev with wireless charge
2022-07-10 Manufactured version of bigboard
2023-08-23 Initial code checkin
2023-08-23 Begin moving bt to mwk
2023-08-29 kernel: ecf: use alternative mechanism for allocation-failure tolerance
    uses fake coroutine frames stored in flash instead of error results.
    In the future, some sort of "error-invariance" trait should be put onto
    the underlying results so that a layout-compatible imposter for the
    result can be used to avoid making unnecessary duplicate constants.
2023-08-29 cmake: use llvm 18
    todo: sync up local coroutine elision patches
2023-08-29 bt: port to using mwk async
    still on the fence about the whole async thing, but it does at least
    work now.
2023-09-08 Begin migrating RP2040 to picolibc w/o picosdk
    still uses the sdk for the hardware_* libs but with carefully selected
    files to avoid bringing too much of it in
    for example, all of the multicore stuff is excluded so we can do it
    ourselves inside the scheduler
2023-09-09 Fix some mwk things
    also use 64 bit tick
2023-09-09 Override openocd's gdb run handling to leave core 1 out of reset
    (in theory it should check the $targetid but meh how often do you want
    to debug core1 startup)
2023-09-09 Hookup __unhandled_user_irq
2023-09-09 Use llvm-objcopy
2023-09-09 Finish porting basic screentester to mwk & migrate to ram dma ctrl buf
    No longer eats the entire 16kib flash cache while scanning out a frame
2023-09-10 Add emulated symmetric transfer mode
    LLVM on armv6m (or anything without thumb-2) has no support for tail
    calls. This causes a few problems, including crashing the compiler when
    trying to use coroutines (fixable with a basic patch) to untenable stack
    overflows, which is what this addresses.
2023-09-10 Force local-exec tls model
    the other models assume dynamic linking which we do not perform, thus
    breaking in a myriad of interesting ways
2023-09-11 Fix screen output
    - dma double buffer was busted
    - adjust VCOM freq to avoid flicker
2023-09-11 Set pads to 1.8V thresholds in crt0
2023-09-11 Dummy BT_INT==5V_EN test power setup
2023-09-11 Test pattern on display
    wow the display works it's incredible
2023-09-11 Fully document screen.pio
2023-10-31 Update board to kicad 7
2023-10-31 Add OS res toolchain
    stolen out of msynth

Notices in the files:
parts and their libraries:
Copyright 2021 Accelerated Designs. All rights reserved.
